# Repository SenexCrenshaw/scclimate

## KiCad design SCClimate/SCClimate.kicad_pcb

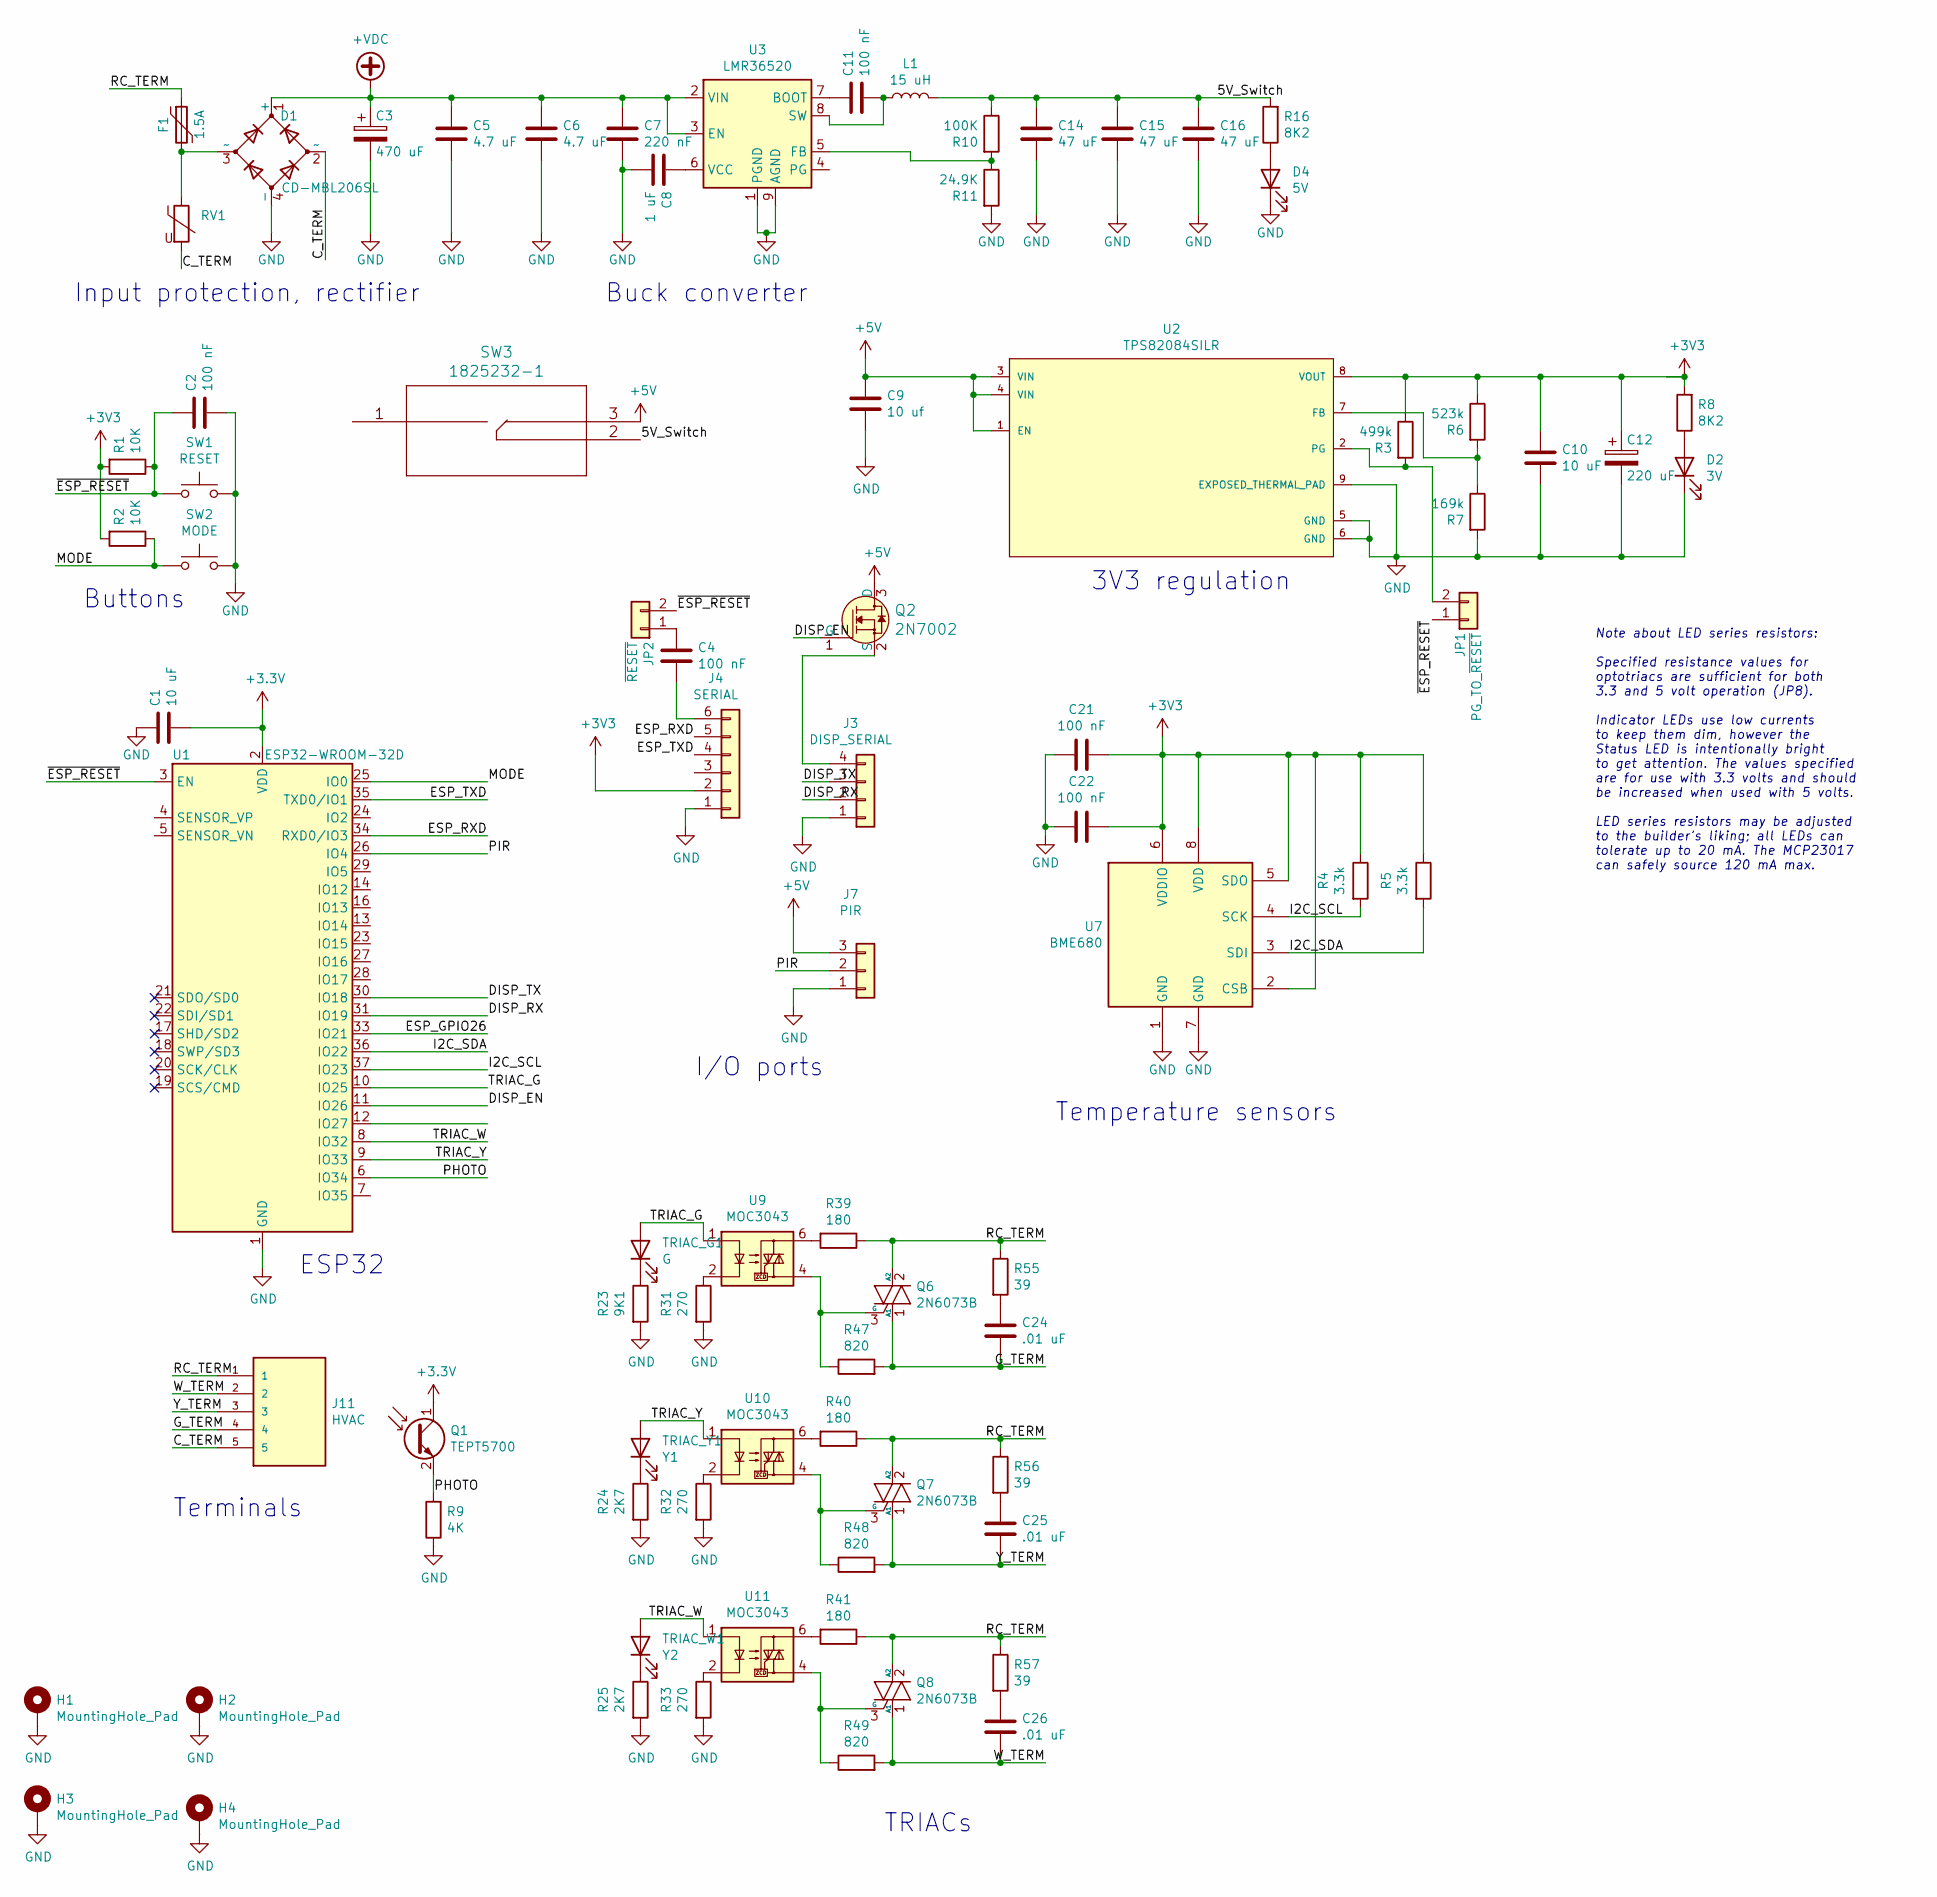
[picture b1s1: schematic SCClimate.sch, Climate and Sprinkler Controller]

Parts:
C1: 10 uF; C_0805_2012Metric; Part C2012X5R1V106K085AC
C2, C4, C11, C21, C22: 100 nF; C_0805_2012Metric; Part CC0805KRX7R7BB104
C3: 470 uF; CP_Elec_16x17.5; Part EEV-FK1H471M
C5, C6: 4.7 uF; C_0805_2012Metric; Part C2012X5R1H475K125AB
C7: 220 nF; C_0805_2012Metric; Part C2012X5R1H224K125AA
C8: 1 uF; C_0805_2012Metric; Part C0805C105K4RACTU
C9: 10 uf; C_0805_2012Metric; Part C0805C106K8PACTU‎
C10: 10 uF; C_0805_2012Metric; Part C0805C106K8PACTU‎
C12: 220 uF; CP_Elec_8x10; Part EEE-HB0J221AP
C14, C15, C16: 47 uF; C_1210_3225Metric; Part GRM32ER61C476KE15L
C24, C25, C26: .01 uF; C_0805_2012Metric; Part CC0805KRX7R9BB103
D1: CD-MBL206SL; Diode_Bridge_Vishay_MBLS; Part CD-MBL206SL
D2: 3V; LED_1206_3216Metric_ReverseMount_Hole1.8x2.4mm; Part 597-6901-607F
D4: 5V; LED_1206_3216Metric_ReverseMount_Hole1.8x2.4mm; Part 597-6901-607F
F1: 1.5A; Fuse_2920_7451Metric; Part 2920L150DR
H1, H2, H3, H4: MountingHole_Pad; MountingHole_3.2mm_M3_DIN965_Pad
J3: DISP_SERIAL; PinSocket_1x04_P2.54mm_Vertical
J4: SERIAL; PinSocket_1x06_P2.54mm_Vertical
J7: PIR; PinHeader_1x03_P2.54mm_Vertical
J11: HVAC; CUI_TBL002A-350-05GY-2GY
JP1: PG_TO_~RESET; PinHeader_1x02_P2.54mm_Vertical
JP2: ~RESET; PinHeader_1x02_P2.54mm_Vertical
L1: 15 uH; L_Wuerth_WE-PD-Typ-LS; Part 7447709150
Q1: TEPT5700; LED_D5.0mm_Clear; Part TEPT5700
Q2: 2N7002; SOT-23-3; MPN 2N7002; Digi-Key_PN 2N7002NCT-ND
Q6, Q7, Q8: 2N6073B; TO-225-3_Vertical; Part 2N6073BG
R1, R2: 10K; R_0805_2012Metric_Pad1.20x1.40mm_HandSolder; Part RC0805FR-0710KL
R3: 499k; R_0805_2012Metric_Pad1.20x1.40mm_HandSolder; Part CRCW0805499KFKEA
R4, R5: 3.3k; R_0805_2012Metric_Pad1.20x1.40mm_HandSolder; Part RT0805FRE07180RL
R6: 523k; R_0805_2012Metric_Pad1.20x1.40mm_HandSolder; Part CRCW0805523KFKEA
R7: 169k; R_0805_2012Metric_Pad1.20x1.40mm_HandSolder; Part CRCW0805169KFKEA
R8, R16: 8K2; R_0805_2012Metric_Pad1.20x1.40mm_HandSolder; Part RT0805FRE078K2L
R9: 4K; R_0805_2012Metric_Pad1.20x1.40mm_HandSolder; Part RC0805FR-07100KL
R10: 100K; R_0805_2012Metric_Pad1.20x1.40mm_HandSolder; Part RC0805FR-07100KL
R11: 24.9K; R_0805_2012Metric_Pad1.20x1.40mm_HandSolder; Part RT0805FRE0724K9L
R23: 9K1; R_0805_2012Metric_Pad1.20x1.40mm_HandSolder; Part RT0805FRE079K1L
R24, R25: 2K7; R_0805_2012Metric_Pad1.20x1.40mm_HandSolder; Part RT0805FRE072K7L
R31, R32, R33: 270; R_0805_2012Metric_Pad1.20x1.40mm_HandSolder; Part RT0805FRE07270RL
R39, R40, R41: 180; R_0805_2012Metric_Pad1.20x1.40mm_HandSolder; Part RT0805FRE07180RL
R47, R48, R49: 820; R_0805_2012Metric_Pad1.20x1.40mm_HandSolder; Part RT0805FRE07820RL
R55, R56, R57: 39; R_0805_2012Metric_Pad1.20x1.40mm_HandSolder; Part ERJ-P06J390V
RV1: B72205S0400K101; RV_Disc_D7mm_W4mm_P5mm; Part B72205S0400K101
SW1: RESET; SW_PUSH_6mm_H8mm; Part PTS645VK582LFS
SW2: MODE; SW_PUSH_6mm_H8mm; Part PTS645VK582LFS
SW3: 1825232-1
TRIAC_G1: G; LED_1206_3216Metric_ReverseMount_Hole1.8x2.4mm; Part APTL3216ZGC
TRIAC_W1: Y2; LED_1206_3216Metric_ReverseMount_Hole1.8x2.4mm; Part APTL3216QBC/D
TRIAC_Y1: Y1; LED_1206_3216Metric_ReverseMount_Hole1.8x2.4mm; Part APTL3216QBC/D
U1: ESP32-WROOM-32D; ESP32-WROOM-32; Part ESP32-WROOM-32D
U2: TPS82084SILR; Texas_Instruments-SIL0008C-0-0-MFG; output voltage 0.8-6V; mouser part number 595-TPS82084SILR; digikey description DC DC CONVERTER 0.8-6V 2A
U3: LMR36520; Texas_HSOP-8-1EP_3.9x4.9mm_P1.27mm_ThermalVias; Part LMR36520ADDAR
U7: BME680; Bosch_LGA-8_3x3mm_P0.8mm_ClockwisePinNumbering
U9, U10, U11: MOC3043; SMDIP-6_W9.53mm; Part MOC3043SM

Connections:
+5V: C9.1, J7.3, Q2.3 (D), SW3.3, U2.1 (EN), U2.3 (VIN), U2.4 (VIN)
+VDC: C3.1, C5.1, C6.1, C7.1, D1.1 (+), U3.2 (VIN), U3.3 (EN)
/5V_Switch: C14.1, C15.1, C16.1, L1.2, R10.1, R16.2, SW3.2
/C_TERM: D1.2 (~~), J11.5, RV1.2
/DISP_EN: Q2.1 (G), U1.11 (IO26)
/DISP_RX: J3.2, U1.31 (IO19)
/DISP_TX: J3.3, U1.30 (IO18)
/ESP_RXD: J4.5, U1.34 (RXD0/IO3)
/ESP_TXD: J4.4, U1.35 (TXD0/IO1)
/G_TERM: C24.2, J11.4, Q6.1 (A1), R47.2
/I2C_SCL: R4.2, U1.37 (IO23), U7.4 (SCK)
/I2C_SDA: R5.2, U1.36 (IO22), U7.3 (SDI)
/MODE: R2.1, SW2.1, U1.25 (IO0)
/PHOTO: Q1.2 (E), R9.2, U1.6 (IO34)
/PIR: J7.2, U1.26 (IO4)
/RC_TERM: F1.1, J11.1, Q6.2 (A2), Q7.2 (A2), Q8.2 (A2), R39.1, R40.1, R41.1, R55.1, R56.1, R57.1
/TRIAC_G: TRIAC_G1.2 (A), U1.10 (IO25), U9.1
/TRIAC_W: TRIAC_W1.2 (A), U1.8 (IO32), U11.1
/TRIAC_Y: TRIAC_Y1.2 (A), U1.9 (IO33), U10.1
/W_TERM: C26.2, J11.2, Q8.1 (A1), R49.2
/Y_TERM: C25.2, J11.3, Q7.1 (A1), R48.2
/~ESP_RESET: C2.1, JP1.1, JP2.2, R1.1, SW1.2, U1.3 (EN)
GND: C1.1, C2.2, C3.2, C5.2, C6.2, C7.2, C8.2, C9.2, C10.2, C12.2, C14.2, C15.2, C16.2, C21.2, C22.2, D1.4 (-), D2.1 (K), D4.1 (K), H1.1, H2.1, H3.1, H4.1, J3.1, J4.1, J7.1, R7.2, R9.1, R11.2, R23.2, R24.2, R25.2, R31.2, R32.2, R33.2, SW1.1, SW2.2, U1.1 (GND), U1.15 (GND), U1.38 (GND), U1.39 (GND), U2.5 (GND), U2.6 (GND), U2.9 (EXPOSED_THERMAL_PAD), U3.1 (PGND), U3.9 (AGND), U7.1 (GND), U7.7 (GND)
unnamed: C4.1, JP2.1
unnamed: C4.2, J4.6
unnamed: C8.1, U3.6 (VCC)
unnamed: C11.1, U3.7 (BOOT)
unnamed: C11.2, L1.1, U3.8 (SW)
unnamed: C24.1, R55.2
unnamed: C25.1, R56.2
unnamed: C26.1, R57.2
unnamed: D1.3 (~~), F1.2, RV1.1
unnamed: D2.2 (A), R8.1
unnamed: D4.2 (A), R16.1
unnamed: J3.4, Q2.2 (S)
unnamed: JP1.2, R3.2, U2.2 (PG)
unnamed: Q6.3 (G), R47.1, U9.4
unnamed: Q7.3 (G), R48.1, U10.4
unnamed: Q8.3 (G), R49.1, U11.4
unnamed: R6.2, R7.1, U2.7 (FB)
unnamed: R10.2, R11.1, U3.5 (FB)
unnamed: R23.1, TRIAC_G1.1 (K)
unnamed: R24.1, TRIAC_Y1.1 (K)
unnamed: R25.1, TRIAC_W1.1 (K)
unnamed: R31.1, U9.2
unnamed: R32.1, U10.2
unnamed: R33.1, U11.2
unnamed: R39.2, U9.6
unnamed: R40.2, U10.6
unnamed: R41.2, U11.6

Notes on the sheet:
Buck converter
3V3 regulation
TRIACs
Terminals
Temperature sensors
I/O ports
ESP32
Buttons
Input protection, rectifier
Note about LED series resistors: Specified resistance values for optotriacs are sufficient for both 3.3 and 5 volt operation (JP8). Indicator LEDs use low currents to keep them dim, however the Status LED is intentionally bright to get attention. The values specified are for use with 3.3 volts and 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

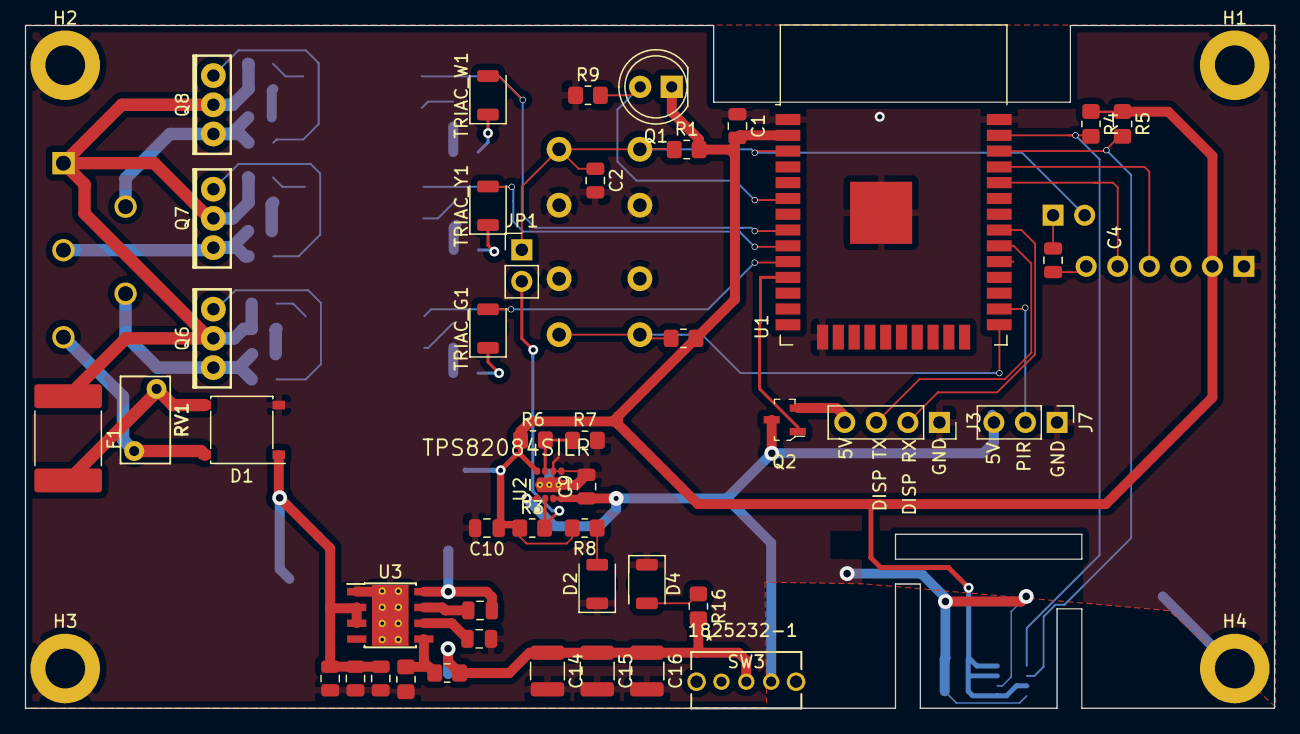
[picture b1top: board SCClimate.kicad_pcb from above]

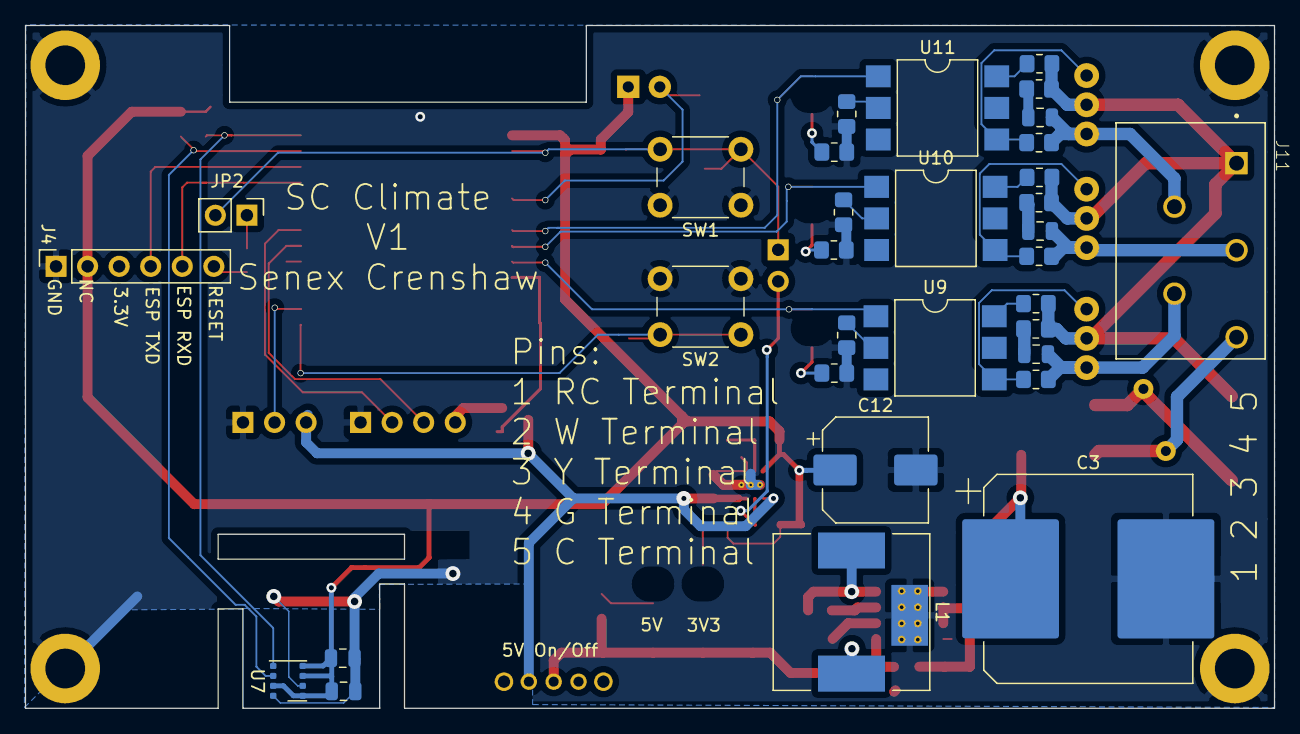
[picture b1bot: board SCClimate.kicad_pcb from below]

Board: 2 copper layers, 100.5 x 54.9 mm, 81 parts (32 on the bottom side), 51 nets.

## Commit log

2020-12-17 Changed a few things around for better placement
2020-12-21 Moved 680 to bottom and switched ldo to buck
2020-12-21 Moved 680 to other side of board

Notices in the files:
parts and their libraries:
Copyright 2016 Accelerated Designs. All rights reserved.
